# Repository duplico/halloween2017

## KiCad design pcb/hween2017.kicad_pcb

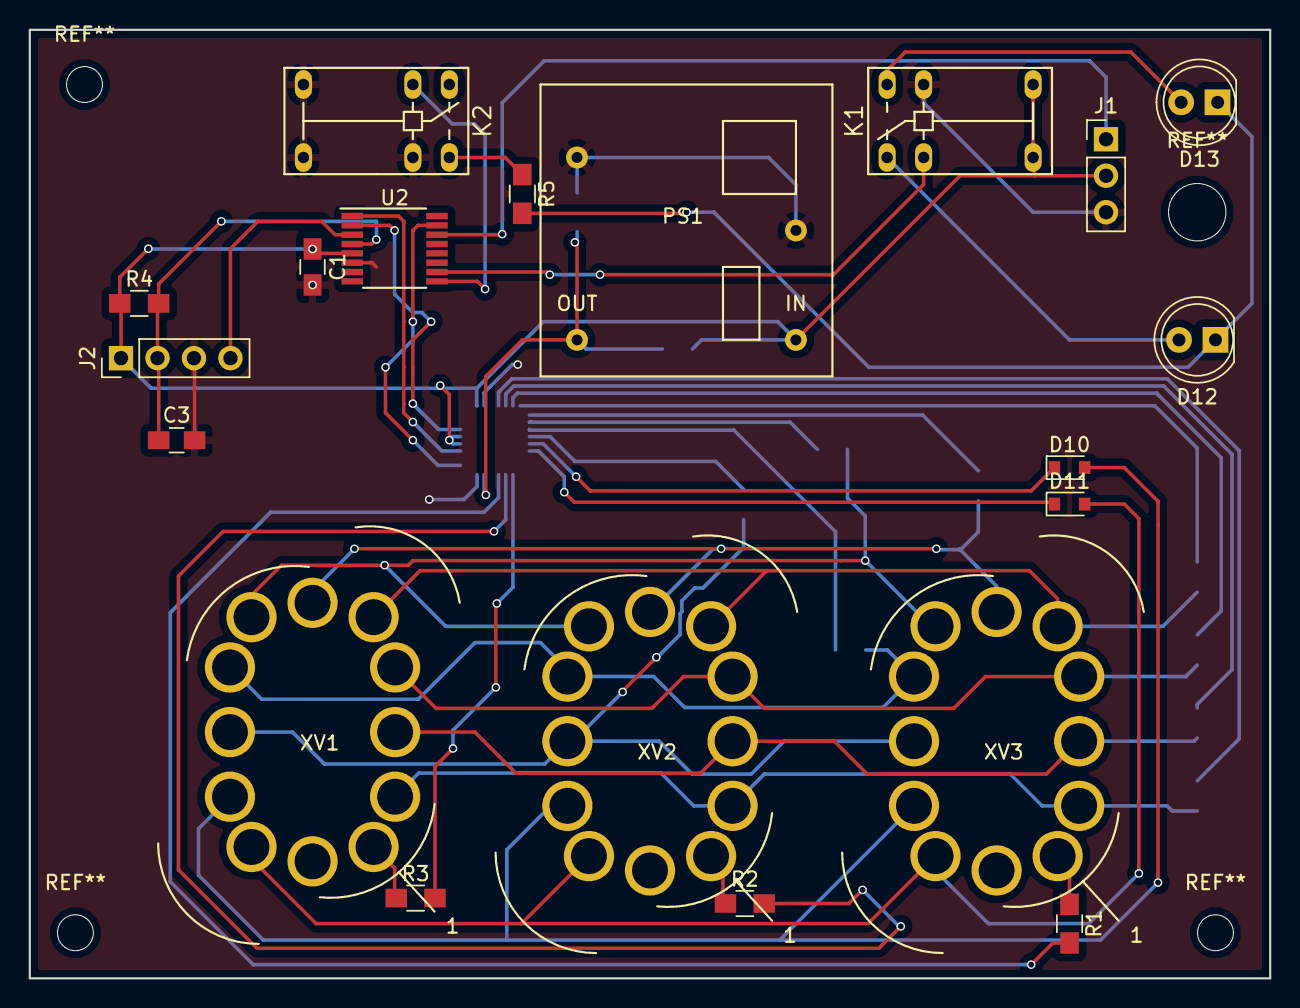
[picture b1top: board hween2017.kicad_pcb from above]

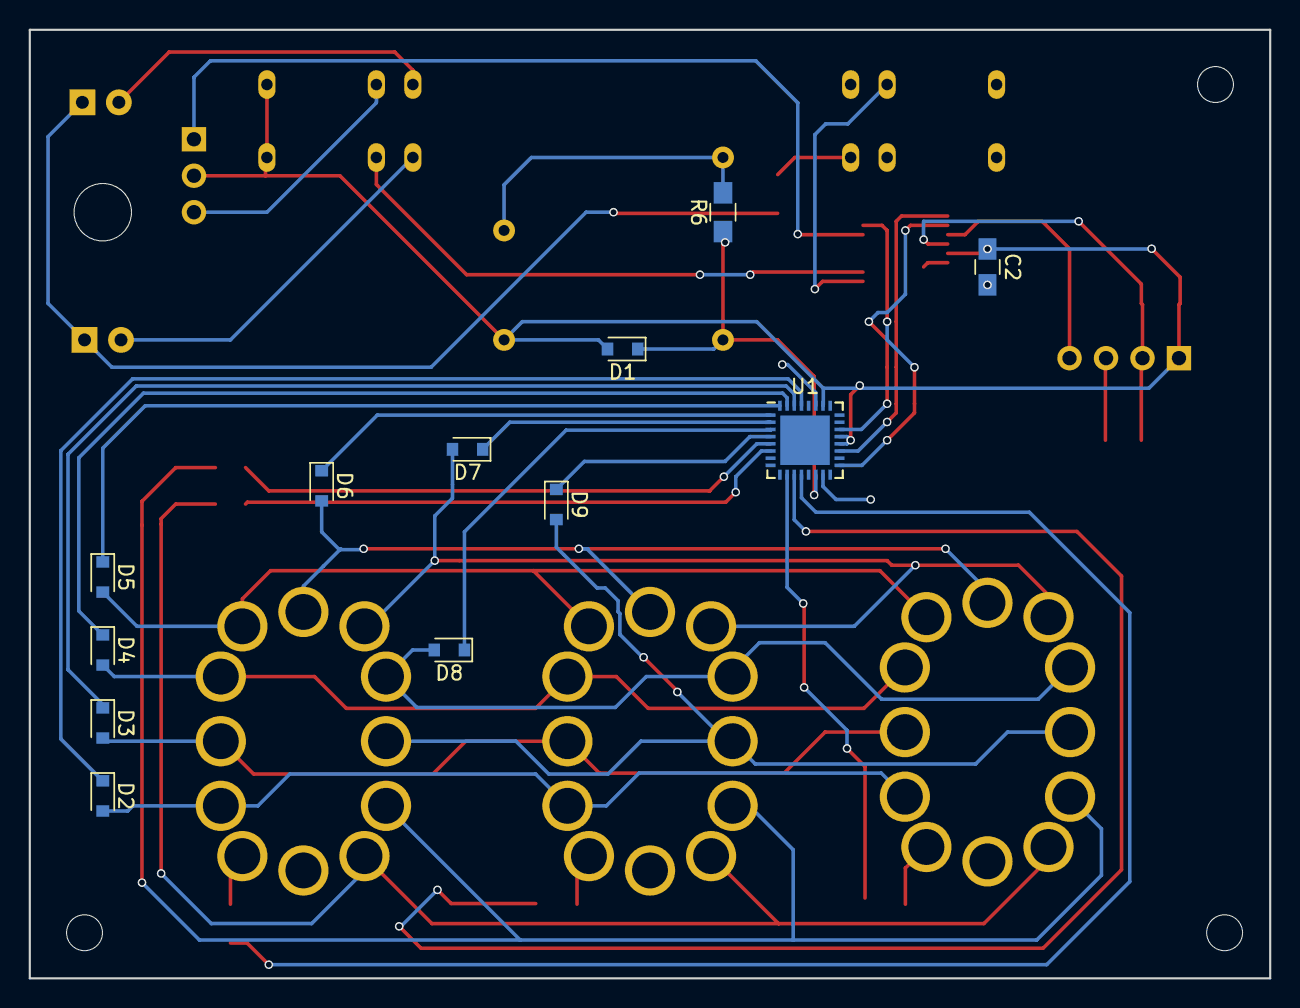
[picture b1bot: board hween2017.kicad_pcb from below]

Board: 2 copper layers, 86.4 x 66.0 mm, 32 parts (12 on the bottom side), 41 nets.

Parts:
C1: 1 uF; C_0805_HandSoldering
C2: 100 nF; C_0805_HandSoldering
C3: 1 nF; C_0805_HandSoldering
D1, D2, D3, D4, D5, D6, D7, D8, D9, D10, D11: D; D_0805
D12, D13: LED; LED_D5.0mm
J1: BATTERY; Pin_Header_Straight_1x03_Pitch2.54mm
J2: JTAG; Pin_Header_Straight_1x04_Pitch2.54mm
K1, K2: SY-3W-K; Fujitsu_Relay_SY-3W-K_SPDT_12.5x7.4
PS1: NCH8200HV
R1, R2, R3: 44 k; R_0805_HandSoldering
R4: 47 k; R_0805_HandSoldering
R5: 1 k; R_0805_HandSoldering
R6: 100k; R_0805_HandSoldering
U1: HV509; QFN-32-1EP_5x5mm_Pitch0.5mm
U2: MSP430FR2100IPW; TSSOP-16_4.4x5mm_Pitch0.65mm
XV1, XV2, XV3: IF-12; IF12

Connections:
/if_0: D2.2, XV1.2, XV2.2, XV3.2
/if_1: D11.2, XV1.11, XV2.11, XV3.11
/if_2: D10.2, XV1.10, XV2.10, XV3.10
/if_3: D9.2, XV1.9, XV2.9, XV3.9
/if_4: D8.2, XV1.8, XV2.8, XV3.8
/if_5: D7.2, XV1.7, XV2.7, XV3.7
/if_6: D6.2, XV1.6, XV2.6, XV3.6
/if_7: D5.2, XV1.5, XV2.5, XV3.5
/if_8: D4.2, XV1.4, XV2.4, XV3.4
/if_9: D3.2, XV1.3, XV2.3, XV3.3
Earth: C1.2, C2.2, C3.2, J1.3, J2.3, K1.9, K2.5, K2.6, K2.9, PS1.2, PS1.3, R6.2, U1.15, U1.27, U2.6
KEY: J1.1, U2.14
L_IN: K1.2, U2.10
L_OUT: K2.2, U2.9
unnamed: D2.1, U1.29
unnamed: D3.1, U1.30
unnamed: D4.1, U1.31
unnamed: D5.1, U1.32
unnamed: D6.1, U1.1
unnamed: D7.1, U1.2
unnamed: D8.1, U1.3
unnamed: D9.1, U1.4
unnamed: D10.1, U1.5
unnamed: D11.1, U1.6
unnamed: D12.1, D13.1, R5.2
unnamed: D12.2, K1.1
unnamed: D13.2, K1.10
unnamed: K2.10, R5.1
unnamed: R1.1, XV3.1
unnamed: R1.2, U1.12
unnamed: R2.1, XV2.1
unnamed: R2.2, U1.11
unnamed: R3.1, XV1.1
unnamed: R3.2, U1.10
unnamed: U1.17, U2.15
unnamed: U1.19, U2.1
unnamed: U1.22, U2.2
RST: C3.1, J2.2, R4.2, U2.4
TEST: J2.4, U2.3
VBAT: C1.1, C2.1, D1.2, J1.2, J2.1, K1.5, K1.6, PS1.1, R4.1, U1.20, U1.21, U1.26, U2.5
VPP: D1.1, PS1.4, R6.1, U1.14

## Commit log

2017-10-11 Initial commit.
2017-10-11 Update ignore.
2017-10-11 Add PBC files.
2017-10-11 Add CCS project.
2017-10-11 Add new PCB changes and a stencil STL file.
2017-10-18 Board is confirmed working.
2017-10-18 Add 3d printed files.
2017-10-18 Add a stand-in schematic design project for the battery board (hand-built)
2017-10-18 Switch to the MSP430FR2111 I had lying around.
2017-10-18 Multiplex~!
2017-10-18 Refactor, add a flicker and some PWM capability.
2017-10-18 Close to final behavior.
2017-10-18 Correct the schematic to as-built.
2017-10-18 Add a model for the base of the case.
2018-02-07 Final as-shipped.
